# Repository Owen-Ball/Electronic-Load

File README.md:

# Overview
 A DIY electronic load capable of 
* CC, CR, CP, Battery (BT) Modes
* 30V, 50mA-7.5A, 120W
* 0-12V @ 3mV resolution, 0-40V @ 10mV resolution
* 0-1A @ 300uA resolution, 0-10A @ 2.5mA resolution

The design uses a custom PCB featuring an ESP32S3 Feather microcontroller. 4 power FETs dissipate the power via a CPU heatsink and current is measured using a bank of power resistors. With proper calibration, measurements/setpoints are within 1% across the entire operational range. 

# To Do Feature List
* Check that the FET that burned is properly secured to heatsink
* CV mode? Not really sure for what application though

# Device Usage
This section provides a brief overview of device operation, including
* An overview of the UI elements
* Using the UI to operate the device
* Some potential pitfalls and things to look out for using the device
* Proper power connections and USB-C connections
## UI Overview
There are 5 "screens" on the UI, corresponding to the 4 operating modes of the device and a calibration screen. These are cycled through with the "mode" (M) button. The current mode is indicated in the top left. On each screen, the output can be enabled with the "enable" (E) button.

On each screen, the top-most value is the setpoint for the mode. This value is changed via the encoder. The 3 values below this are the measured values, which consist of the voltage, current, and either the power or discharged mAh in the case of battery mode. The temperature is also displayed at the bottom, along with any error messages. The output state is indicated by a red (off) or green (on) circle in the bottom right.

## Firmware Operation
On each screen, the rotary encoder can be used to change the setpoint within the system bounds. The place value being edited can be changed by clicking the encoder to cycle through place values, or by pressing down the encoder and turning it.

Once on the desired mode and with the correct setpoint, the enable button can be used to toggle the system output. The output indicator will turn green. If the output turns off unexpectedly, an error/warning message should be displayed indicating the reason, with most of these going away next time the enable button is pressed.

All modes operate in general by very roughly setting a current, maybe with 10-25% accuracy. The actual current is monitored and used to adjust the setpoint. This is done with an integral controller, which requires some sanity checking to ensure system safety. If there is no source connected (or it is underpowered), the system will detect this and shut off the output. More specifically, if the set current and measured current are not within a certain tolerance of each other for a set amount of time, the output is disabled.

Other reasons for system shutoff are voltage or temperature limits being exceeded. In CR or CP modes, since the current is automatically calculated the output will be shut off if the system tries to set the current or power above the system limit.

In rare circumstances the system can oscillate. This will occur in the presence of a slow responding source in series (ie an incandescent bulb) or through interactions with the feedback system of a power supply. There is no protection against this, so turn the system off if observed.

## Hardware Operation
While the system has some reverse polarity protection, it is highly recommended that this is not relied on. As such, make sure to connect the higher potential of the source to the +/red terminal and the lower to the -/black terminal. While the system should draw no current while powered off, I recommend having the system powered before connecting a source.

When connecting to the Feather using a USB-C cable, a cable with the 5V line cut is recommended. The system has diodes on the 5V lines so there are no shorting risks, but for some reason the system measurements differ by around 1% depending on whether the system receives USB power or not. Thus for calibration using the serial monitor, a cable with no power is essential. 

The system can be put into bootloader mode by pressing down the encoder while turning on the system (assuming you bridge the encoder pin and bootloader testpad on the feather together).

Additionally, please use caution when operating the device, as mains 120V power is used. There are potential areas of risk, including power supply failure and improper crimping for the live wires.

# Hardware

## Microcontroller

The microcontroller used is the ESP32S3 feather. This was done with the intention of adding WiFi support to the device for the monitoring and setting of parameters. However, the ESP32S3 has issues using both the ADC and WiFi at the same time, so this feature is on hold. Additionally, I did not have any significant use cases for the WiFi anyways. If not implementing WiFi functionality, the ESP32 is a poor choice due to the extremely non-linear ADCs that mandate extensive calibration.

## Power Components:
The bulk of the power is burned using 4 [IRFB7545PBF](https://www.digikey.com/en/products/detail/infineon-technologies/IRFB7545PBF/4772483?_gl=1*qid4uc*_up*MQ..&gclid=CjwKCAiAmfq6BhAsEiwAX1jsZwDCxFQFxVeq3aHN9mwHQtf8dV56gFwLjNTAg517n_BBnAF4h2P2nxoCqRcQAvD_BwE&gclsrc=aw.ds) NCH MOSFETs (TO-220). The FETs are mounted to a [CPU heatsink](https://www.amazon.com/dp/B00006B8EX?ref=ppx_yo2ov_dt_b_fed_asin_title&th=1) to thermally couple them and provide power dissipation. Current measurements are done using the voltage across banks of [RSMF2JT4R70](https://www.digikey.com/en/products/detail/stackpole-electronics-inc/RSMF2JT4R70/2021732?_gl=1*1e5c9mv*_up*MQ..&gclid=CjwKCAiAmfq6BhAsEiwAX1jsZwDCxFQFxVeq3aHN9mwHQtf8dV56gFwLjNTAg517n_BBnAF4h2P2nxoCqRcQAvD_BwE&gclsrc=aw.ds) 4.7 Ohm resistors. Each FET is in series with a bank of 4 of these resistors in parallel. The resistors are cooled via a fan mounted to the system case.

A 10A fuse is placed in series with the + input to the system. Some degree of reverse polarity protection is present in the form of a reverse biased diode across the input ports after the fuse. This ideally will limit reverse voltages to less than 1V but has not been tested.

## Sensing
All sensing is done via the ADCs on the ESP32S3. Accurary could be improved by purchasing more accurate standalone ICs for voltage and current measurements however. 

Voltage sensing has two ranges, 0-12V and 0-<span style="color:red"> 40V (need to check)</span>. Thus for a 12-bit ADC, resolution is around 3mV/step and 10mV/step. Both sensors operate using a simple voltage divider to divide down the max voltage to the maximum ADC input of ~3.2V. 7.5V zener diodes are used to clamp the voltage input to the ADCs to ~3.75V. 7.5V zeners are used since lower voltage zeners feature a less sharp turn on that would increase leakage and worsen the voltage clamping. One note is the pin used for the high voltage range on the ESP32S3 feather has an SMD LED attached to it (not sure why they put the on-board LED on an analog in pin...). For high voltage inputs, this drives the LED, which is not ideal and causes non-linearity in the measurement that needs to be compensated for. The LED could of course be removed, but I did not do this.

Current sensing is done with two ranges as well, although there are some major design oversights. The original intention was to have two operating modes, one where all 4 FETs were running and one were only a single one was active. This would enable higher precision for low current measurements. Thus 3 of the 4 FETs are controlled by 1 DAC and the final one is controlled by a separate DAC. 

The high sensitivity current sensor amplies the voltage across the power resistors by a factor of 10. Thus for 16 shunt resistors, this range maxes out around 1.1A. The design oversight is that this sensor is only hooked up to the independently controlled FET path, so in high current mode, this sensor is not truly measuring the current, it is "guessing" based on a measurement of 1/4 of the current.

The low sensitivity (higher range) current sensor uses resistors to average the voltages across the 4 shunts. This means it works properly in high current mode, but not in low, since this setup will not work when only the one FET is active. This mode peaks at around <span style="color:red"> 10A (need to check)</span>.

As a summary of the design oversights, the only fully functioning current sensing modes would be high current mode + low sensitivity sensor and low current mode, high sensitivity sensor. After discovering this issue, I cut support for low current mode entirely since I currently do not have a use case for the latter mode (would be 0-250mA), although this may be added in the future. I did decide to use the high sensitivity current sensor is used in high current mode despite only directly measuring 1/4 of the current.

# Firmware Details
More details regarding the firmware implementation can be found in the firmware-specific readme
[here](./Firmware/Firmware_ReadMe.md)

This includes:
* Error codes
* Feedback loops
* System FSM
* Calibration
* Setup

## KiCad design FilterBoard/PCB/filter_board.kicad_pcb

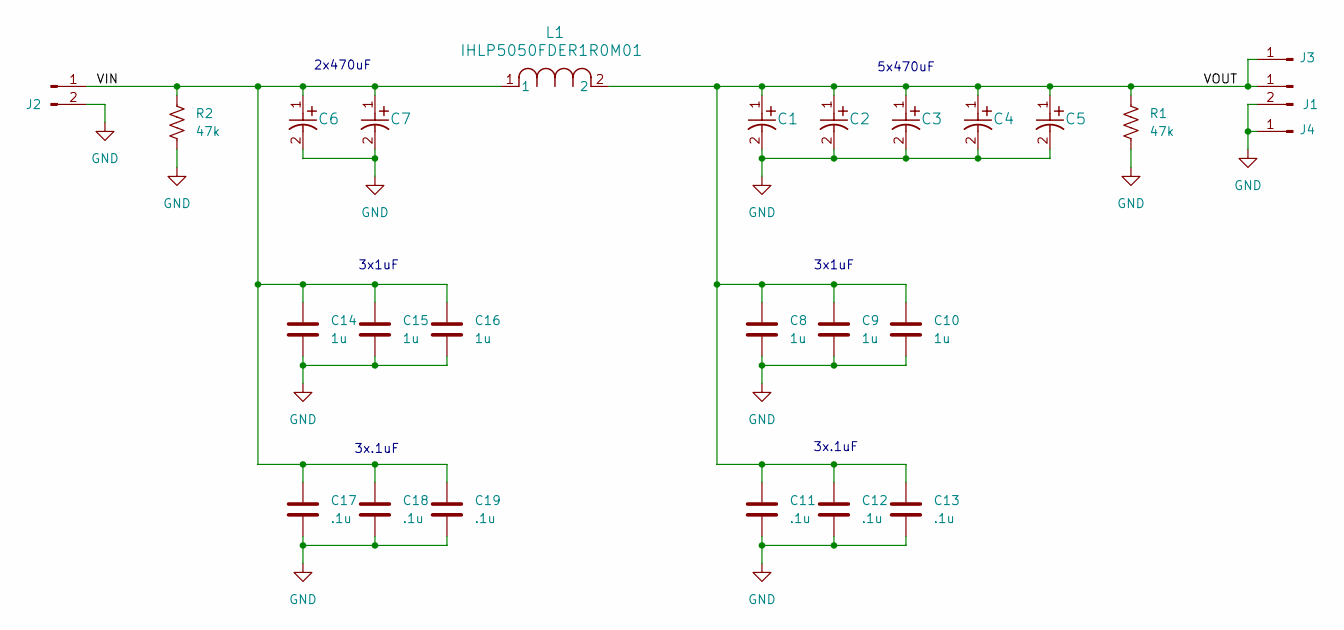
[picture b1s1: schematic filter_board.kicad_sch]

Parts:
C1, C2, C3, C4, C5, C6, C7: EMHB630ARA471MMH0S
C8, C9, C10, C14, C15, C16: 1u; C_0805_2012Metric
C11, C12, C13, C17, C18, C19: .1u; C_0805_2012Metric
J1: Banana_Terminals
J2: Banana Terminals; Banana_Terminals
J3, J4: Conn_01x01_Pin; Wire_Pad
L1: IHLP5050FDER1R0M01; IND_IHLP-5050FD-01_VIS
R1, R2: 47k; R_0805_2012Metric

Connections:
/VIN: C6.1, C7.1, C14.1, C15.1, C16.1, C17.1, C18.1, C19.1, J2.1, L1.1, R2.1
/VOUT: C1.1, C2.1, C3.1, C4.1, C5.1, C8.1, C9.1, C10.1, C11.1, C12.1, C13.1, J1.1, J3.1, L1.2, R1.1
GND: C1.2, C2.2, C3.2, C4.2, C5.2, C6.2, C7.2, C8.2, C9.2, C10.2, C11.2, C12.2, C13.2, C14.2, C15.2, C16.2, C17.2, C18.2, C19.2, J1.2, J2.2, J4.1, R1.2, R2.2

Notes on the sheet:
2x470uF
3x.1uF
5x470uF
3x1uF

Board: 2 copper layers, 26 parts (0 on the bottom side), 3 nets, no tracks yet.

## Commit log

2024-06-16 Renamed main arduino file
2024-06-17 Added CR and CP functionality
    Added constant resistance and power modes. Need to fix the setpoint being kept constant between modes and need to add protection to shut the output off if the desired setpoint cannot be achieved.
2024-06-28 Sped up main loop, added filtering to display measurements, parametrized text location
2024-06-28 Fixed some potential div by 0 issues and commented constants.h
2024-06-29 Screen refresh rate, placeholder for CV
    Added a screen refresh rate limit so the main loop can run fast while maintaining a reasonable refresh rate of values
    Added a placeholder for CV since the output would not shut off when switching to CV while output was on
2024-06-29 Added placeholder CV function to header file
2024-06-29 Added constant for CR, CP, CV filter
2024-07-21 Beginning implementation of battery discharge mode
2024-07-25 Initial implementation of battery discharge mode
2024-07-25 Debug function for printing values without USB
2024-07-27 Individual setpoint for each mode
2024-12-14 Enforce system limits, new fan curves
    Shut down system when max power, current, or voltage exceeded (although doesn't really help in the case of voltage)
    Updated fan profile to also factor in current, not just heat sink temperature
    Remapped I/O buttons
2024-12-16 Lowered power limit, started readme
    Attempted very brief operation at 180W, instantly smoked a FET. Lowered power limit from 135W to 120W as a precaution, despite no issues being observed at 135W.
    Also lowered max current to be same as current setpoint, I don't really want the system going above 7.5A
    Started README file
2024-12-16 Untested safety code + error status
    Implemented check of agreement between the two current sensors.
    Also began implementation of error flags, although they currently cannot be accessed (will display error codes on screen in future update)
2024-12-17 Moved Button Library, work on error msg
    Added untested error printing code
    Also moved Button library from my libraries folder to the repository since it was modified slightly
2024-12-24 Print temperature and bypass CV mode
    Print temperature to screen, added overtemp error, and bypass CV mode when using the Mode button
2024-12-24 Reorganized repository
2024-12-24 Added CAD folder
2024-12-24 Readme updates
2024-12-30 Creating firmware readme, put ino file in folder
2025-01-04 Updated firmware setup info
    tried to compile on new system and realized some issues with the Arduino setup information
2025-01-04 Operational modes info
2025-01-26 Adding filter board KiCAD files
    external filter board to reduce the large ripple currents the Eload produces
2025-02-01 Filter board layout tweaks
2025-03-30 Added cal mode to eload + work on filter board
    Added a cal mode to correct for resistive drops on wires. Also some updates to the filter board PCB
2025-03-30 Fixed small typo in readme
2025-04-25 fixed internal R calibration
    Internal R calibration was only applied to displayed values, it wasn't used for setpoint calcs
